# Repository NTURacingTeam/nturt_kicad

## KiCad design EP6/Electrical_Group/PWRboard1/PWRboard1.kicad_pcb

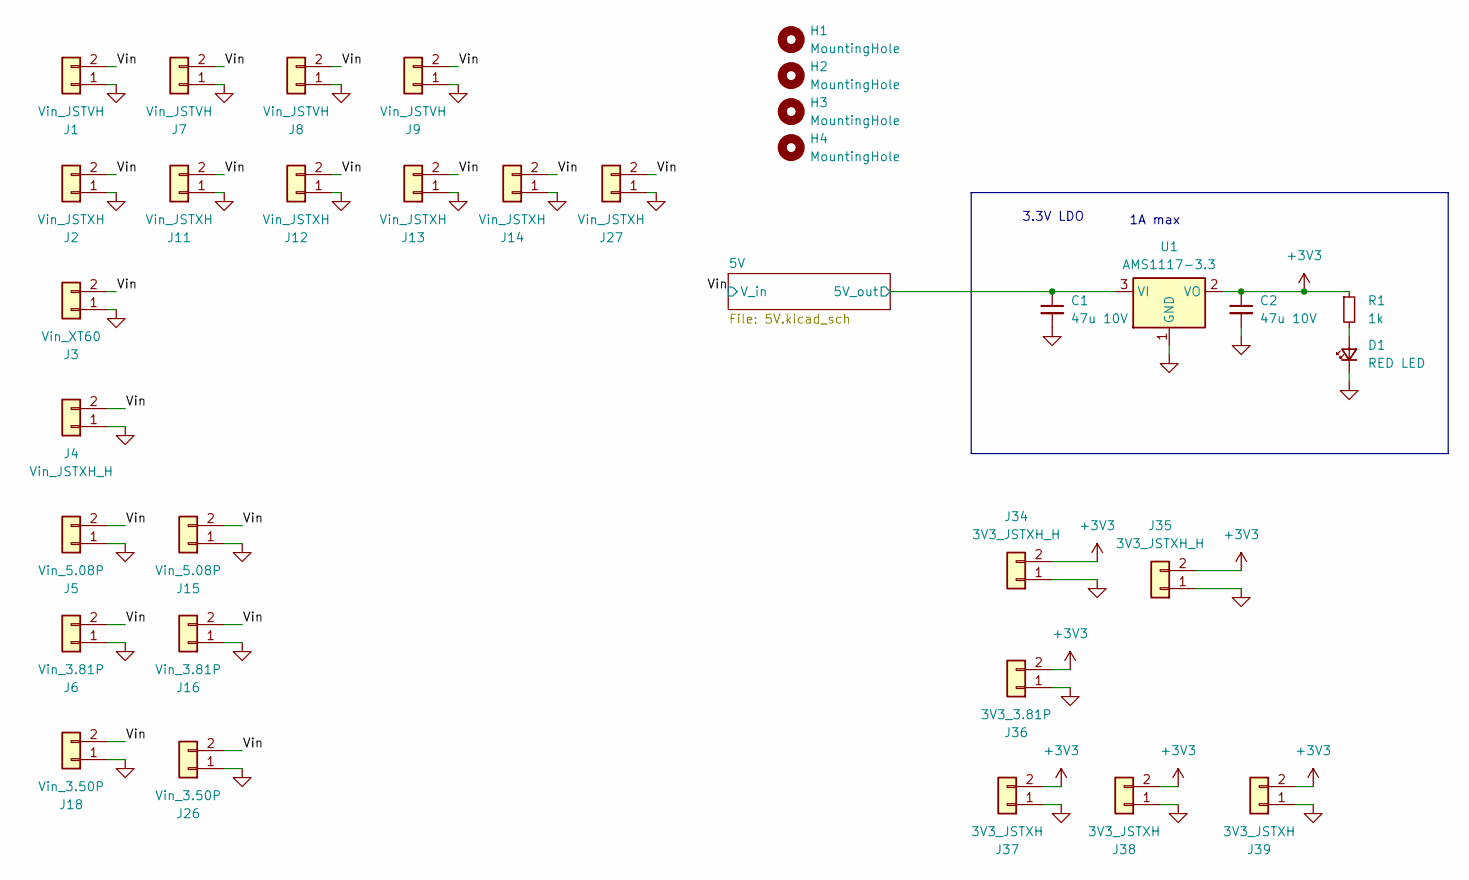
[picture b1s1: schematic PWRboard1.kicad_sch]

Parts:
C1, C2: 47u 10V; C_1206_3216Metric
D1: RED LED; LED_0603_1608Metric
H1, H2, H3, H4: MountingHole; MountingHole_3.2mm_M3
J1, J7, J8, J9: Vin_JSTVH; JST_VH_B2P-VH_1x02_P3.96mm_Vertical
J2, J11, J12, J13, J14, J27: Vin_JSTXH; JST_XH_B2B-XH-A_1x02_P2.50mm_Vertical
J3: Vin_XT60; AMASS_XT60PW-M_1x02_P7.20mm_Horizontal
J4: Vin_JSTXH_H; JST_XH_S2B-XH-A_1x02_P2.50mm_Horizontal
J5, J15: Vin_5.08P; PhoenixContact_MSTBA_2,5_2-G-5,08_1x02_P5.08mm_Horizontal
J6, J16: Vin_3.81P; PhoenixContact_MC_1,5_2-G-3.81_1x02_P3.81mm_Horizontal
J18, J26: Vin_3.50P; PhoenixContact_MC_1,5_2-G-3.5_1x02_P3.50mm_Horizontal
J34, J35: 3V3_JSTXH_H; JST_XH_S2B-XH-A_1x02_P2.50mm_Horizontal
J36: 3V3_3.81P; PhoenixContact_MC_1,5_2-G-3.81_1x02_P3.81mm_Horizontal
J37, J38, J39: 3V3_JSTXH; JST_XH_B2B-XH-A_1x02_P2.50mm_Vertical
R1: 1k; R_0402_1005Metric
U1: AMS1117-3.3; SOT-223-3_TabPin2

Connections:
+3V3: C2.1, J34.2, J35.2, J36.2, J37.2, J38.2, J39.2, R1.1, U1.2 (VO)
/5V/+5V_buck: C1.1, U1.3 (VI); also elsewhere on the board
/Vin: J1.2, J2.2, J3.2, J4.2, J5.2, J6.2, J7.2, J8.2, J9.2, J11.2, J12.2, J13.2, J14.2, J15.2, J16.2, J18.2, J26.2, J27.2; also elsewhere on the board
GND: C1.2, C2.2, D1.1 (K), J1.1, J2.1, J3.1, J4.1, J5.1, J6.1, J7.1, J8.1, J9.1, J11.1, J12.1, J13.1, J14.1, J15.1, J16.1, J18.1, J26.1, J27.1, J34.1, J35.1, J36.1, J37.1, J38.1, J39.1, U1.1 (GND); also elsewhere on the board
unnamed: D1.2 (A), R1.2

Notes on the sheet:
1A max
3.3V LDO

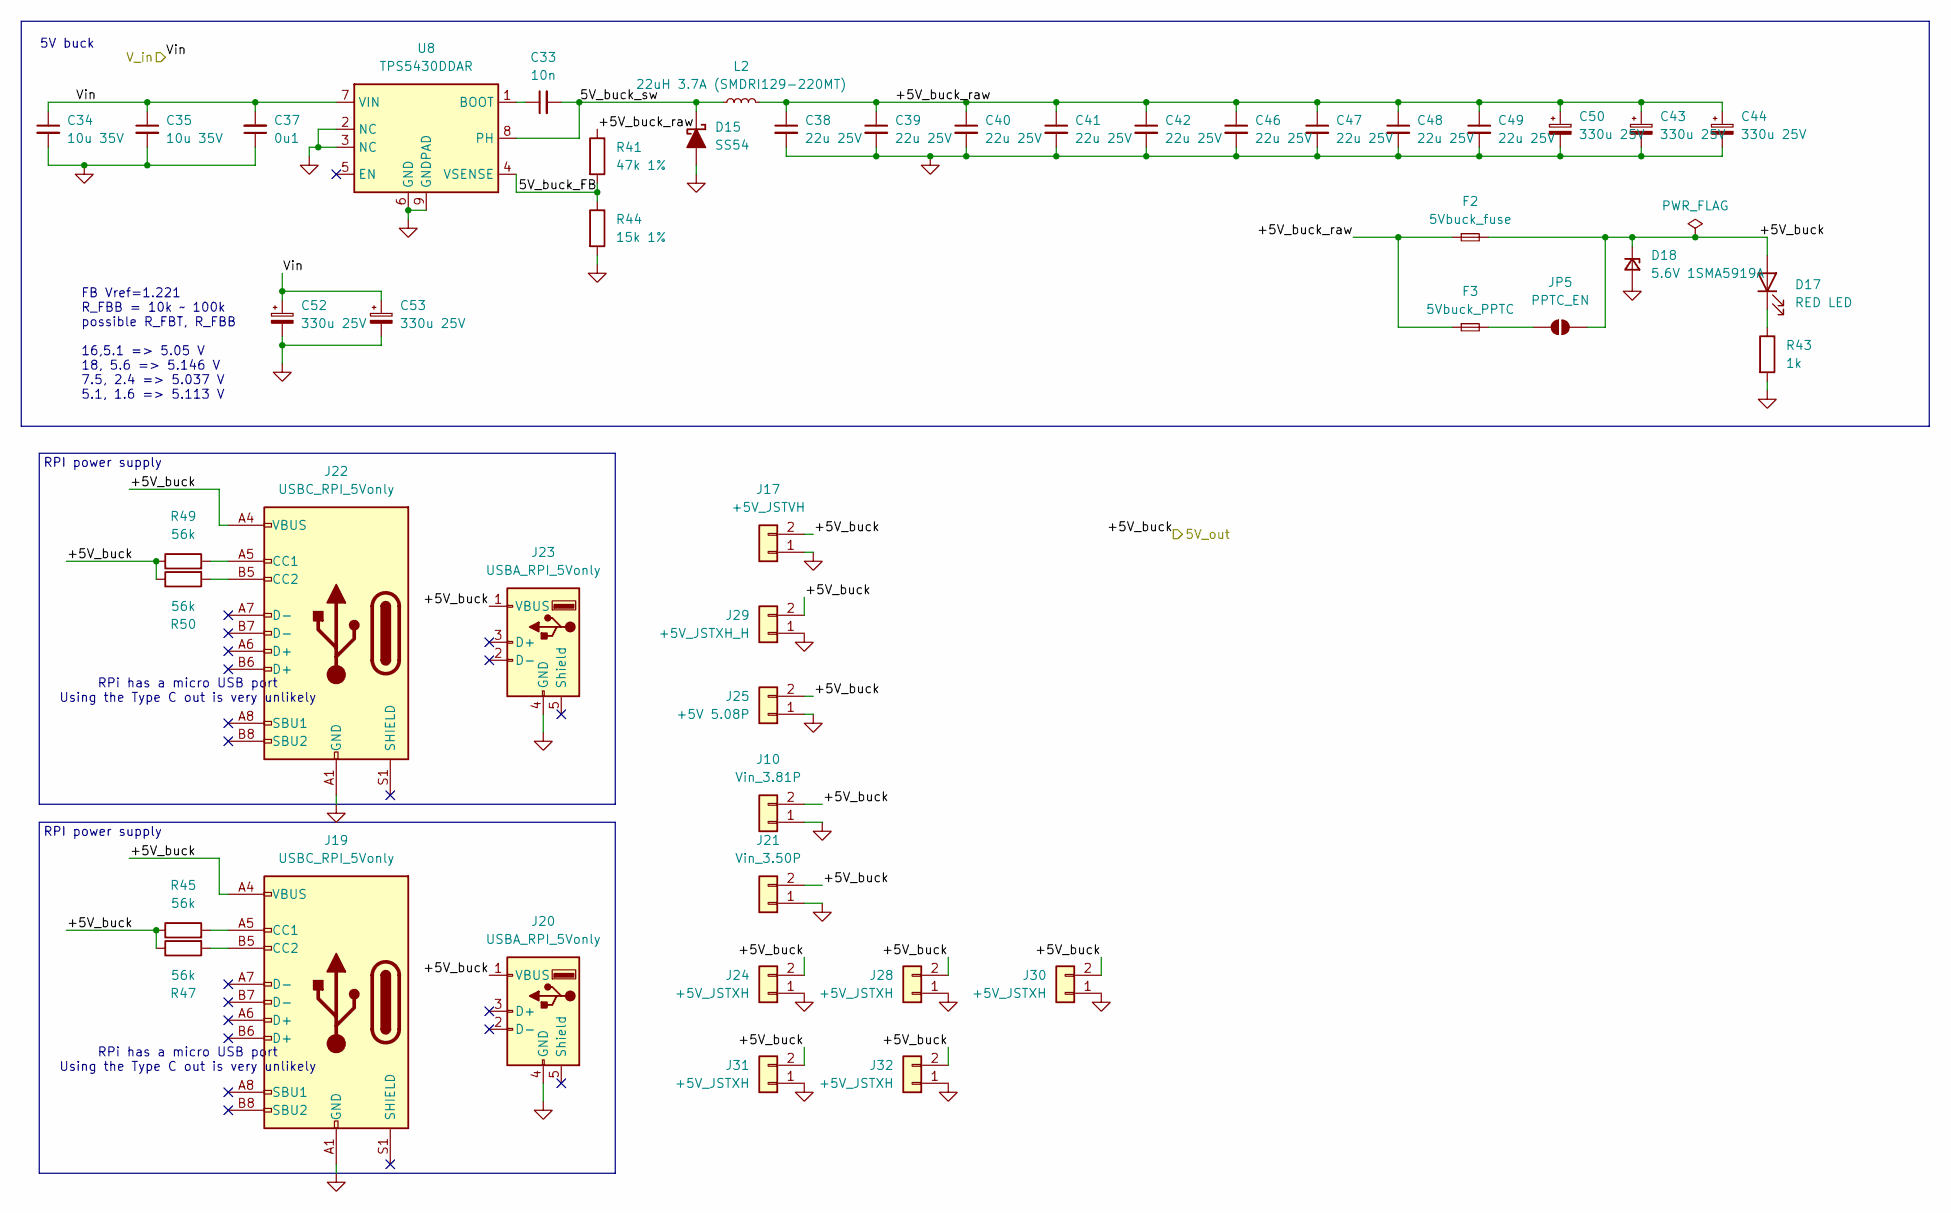
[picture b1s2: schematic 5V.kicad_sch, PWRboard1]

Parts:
C33: 10n; C_0603_1608Metric
C34, C35: 10u 35V; C_1206_3216Metric
C37: 0u1; C_0603_1608Metric
C38, C39, C40, C41, C42, C46, C47, C48, C49: 22u 25V; C_1206_3216Metric
C43, C44, C50, C52, C53: 330u 25V; CP_Radial_D8.0mm_P3.80mm
D15: SS54; D_SMA
D17: RED LED; LED_0603_1608Metric
D18: 5.6V 1SMA5919A; D_SMA
F2: 5Vbuck_fuse; Fuseholder_Cylinder-5x20mm_Stelvio-Kontek_PTF78_Horizontal_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
F3: 5Vbuck_PPTC; Fuse_1206_3216Metric
J10: Vin_3.81P; PhoenixContact_MC_1,5_2-G-3.81_1x02_P3.81mm_Horizontal
J17: +5V_JSTVH; JST_VH_B2P-VH_1x02_P3.96mm_Vertical
J19, J22: USBC_RPI_5Vonly; USB_C_Receptacle_GCT_USB4105-xx-A_16P_TopMnt_Horizontal
J20, J23: USBA_RPI_5Vonly; USB_A_Molex_67643_Horizontal
J21: Vin_3.50P; PhoenixContact_MC_1,5_2-G-3.5_1x02_P3.50mm_Horizontal
J24, J28, J30, J31, J32: +5V_JSTXH; JST_XH_B2B-XH-A_1x02_P2.50mm_Vertical
J25: +5V 5.08P; PhoenixContact_MSTBA_2,5_2-G-5,08_1x02_P5.08mm_Horizontal
J29: +5V_JSTXH_H; JST_XH_S2B-XH-A_1x02_P2.50mm_Horizontal
JP5: PPTC_EN; SolderJumper-2_P1.3mm_Open_RoundedPad1.0x1.5mm
L2: 22uH 3.7A (SMDRI129-220MT); L_Bourns_SRR1260
R41: 47k 1%; R_0603_1608Metric
R43: 1k; R_0402_1005Metric
R44: 15k 1%; R_0603_1608Metric
R45, R47, R49, R50: 56k; R_0402_1005Metric
U8: TPS5430DDAR; TI_SO-PowerPAD-8_ThermalVias

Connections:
/5V/5V_buck_FB: R41.2, R44.1, U8.4 (VSENSE)
/5V/5V_buck_sw: C33.2, D15.1 (K), L2.1, U8.8 (PH)
/5V/+5V_buck: D17.2 (A), D18.1 (K), F2.2, J10.2, J17.2, J19.A4 (VBUS), J19.A9 (VBUS), J19.B4 (VBUS), J19.B9 (VBUS), J20.1 (VBUS), J21.2, J22.A4 (VBUS), J22.A9 (VBUS), J22.B4 (VBUS), J22.B9 (VBUS), J23.1 (VBUS), J24.2, J25.2, J28.2, J29.2, J30.2, J31.2, J32.2, JP5.2 (B), R45.1, R47.1, R49.1, R50.1; also elsewhere on the board
/5V/+5V_buck_raw: C38.1, C39.1, C40.1, C41.1, C42.1, C43.1, C44.1, C46.1, C47.1, C48.1, C49.1, C50.1, F2.1, F3.1, L2.2, R41.1
/Vin: C34.1, C35.1, C37.2, C52.1, C53.1, U8.7 (VIN); also elsewhere on the board
GND: C34.2, C35.2, C37.1, C38.2, C39.2, C40.2, C41.2, C42.2, C43.2, C44.2, C46.2, C47.2, C48.2, C49.2, C50.2, C52.2, C53.2, D15.2 (A), D18.2 (A), J10.1, J17.1, J19.A1 (GND), J19.A12 (GND), J19.B1 (GND), J19.B12 (GND), J20.4 (GND), J21.1, J22.A1 (GND), J22.A12 (GND), J22.B1 (GND), J22.B12 (GND), J23.4 (GND), J24.1, J25.1, J28.1, J29.1, J30.1, J31.1, J32.1, R43.2, R44.2, U8.2 (NC), U8.3 (NC), U8.6 (GND), U8.9 (GNDPAD); also elsewhere on the board
unnamed: D17.1 (K), R43.1
unnamed: J19.A5 (CC1), R45.2
unnamed: J19.B5 (CC2), R47.2
unnamed: J22.A5 (CC1), R49.2
unnamed: J22.B5 (CC2), R50.2
unnamed: F3.2, JP5.1 (A)
unnamed: C33.1, U8.1 (BOOT)

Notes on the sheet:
RPi has a micro USB port Using the Type C out is very unlikely
5V buck
RPI power supply
FB Vref=1.221 R_FBB = 10k ~ 100k possible R_FBT, R_FBB 16,5.1 => 5.05 V 18, 5.6 => 5.146 V 7.5, 2.4 => 5.037 V 5.1, 1.6 => 5.113 V

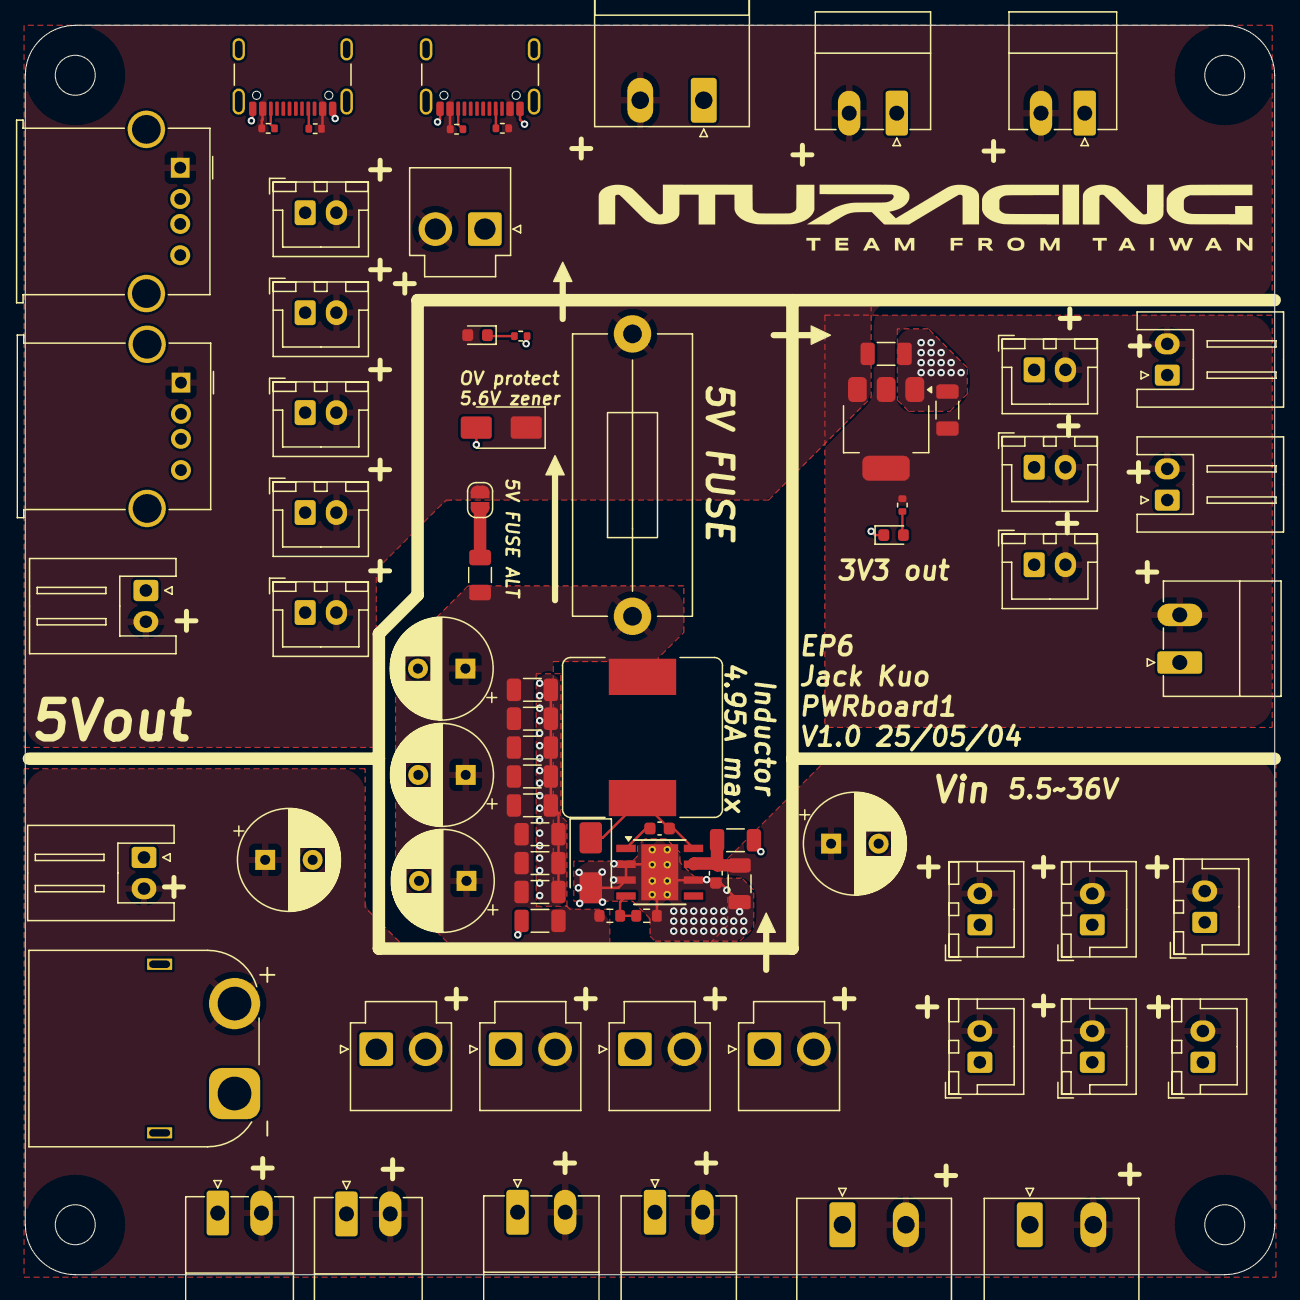
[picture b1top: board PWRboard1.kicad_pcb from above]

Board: 2 copper layers, 100.0 x 100.0 mm, 80 parts (0 on the bottom side), 15 nets.

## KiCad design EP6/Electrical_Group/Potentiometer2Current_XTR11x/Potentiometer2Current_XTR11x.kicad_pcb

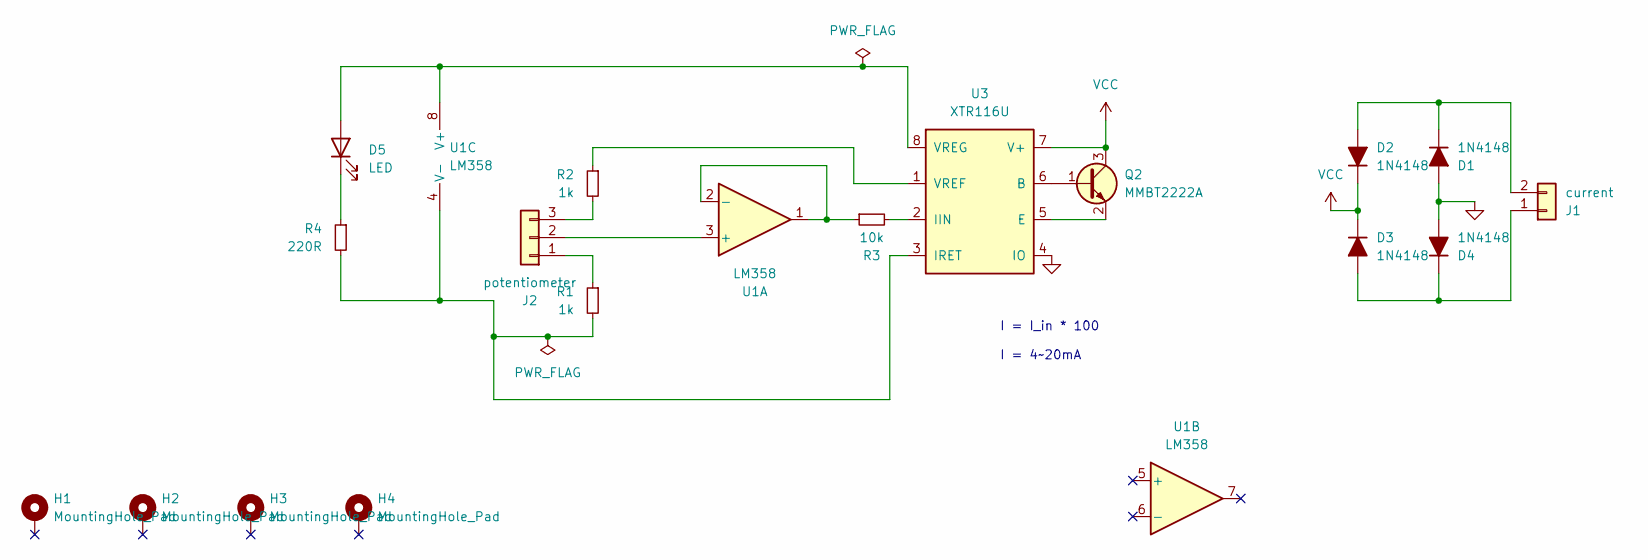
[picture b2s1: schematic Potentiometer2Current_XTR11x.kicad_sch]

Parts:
D1, D2, D3, D4: 1N4148; D_SOD-323
D5: LED; LED_0603_1608Metric
H1, H2, H3, H4: MountingHole_Pad; MountingHole_3.2mm_M3_Pad_TopBottom
J1: current; JST_XH_S2B-XH-A_1x02_P2.50mm_Horizontal; Part Number 1-0201FBV0T
J2: potentiometer; JST_XH_S3B-XH-A_1x03_P2.50mm_Horizontal
Q2: MMBT2222A; SOT-23
R1, R2: 1k; R_0402_1005Metric
R3: 10k; R_0402_1005Metric
R4: 220R; R_0402_1005Metric
U1: LM358; SOIC-8_3.9x4.9mm_P1.27mm
U3: XTR116U; SOIC-8_3.9x4.9mm_P1.27mm

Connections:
GND: D1.2 (A), D4.2 (A), U3.4 (IO)
unnamed: D1.1 (K), D2.2 (A), J1.2
unnamed: D3.2 (A), D4.1 (K), J1.1
unnamed: D5.2 (A), U1.8 (V+), U3.8 (VREG)
unnamed: D5.1 (K), R4.1
unnamed: J2.1, R1.1
unnamed: J2.2, U1.3 (+)
unnamed: J2.3, R2.2
unnamed: Q2.1 (B), U3.6 (B)
unnamed: Q2.2 (E), U3.5 (E)
unnamed: R3.1, U1.1, U1.2 (-)
unnamed: R1.2, R4.2, U1.4 (V-), U3.3 (IRET)
unnamed: R3.2, U3.2 (IIN)
unnamed: R2.1, U3.1 (VREF)
VCC: D2.1 (K), D3.1 (K), Q2.3 (C), U3.7 (V+)

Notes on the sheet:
I = I_in * 100 I = 4~20mA

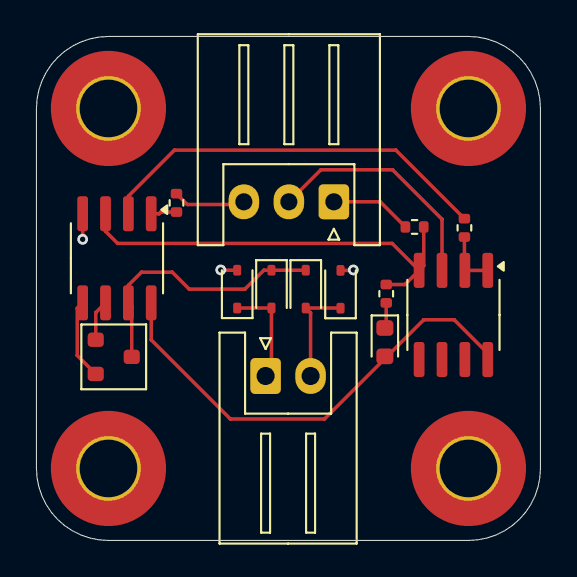
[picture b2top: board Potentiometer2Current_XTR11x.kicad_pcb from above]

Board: 2 copper layers, 28.0 x 28.0 mm, 18 parts (0 on the bottom side), 15 nets.

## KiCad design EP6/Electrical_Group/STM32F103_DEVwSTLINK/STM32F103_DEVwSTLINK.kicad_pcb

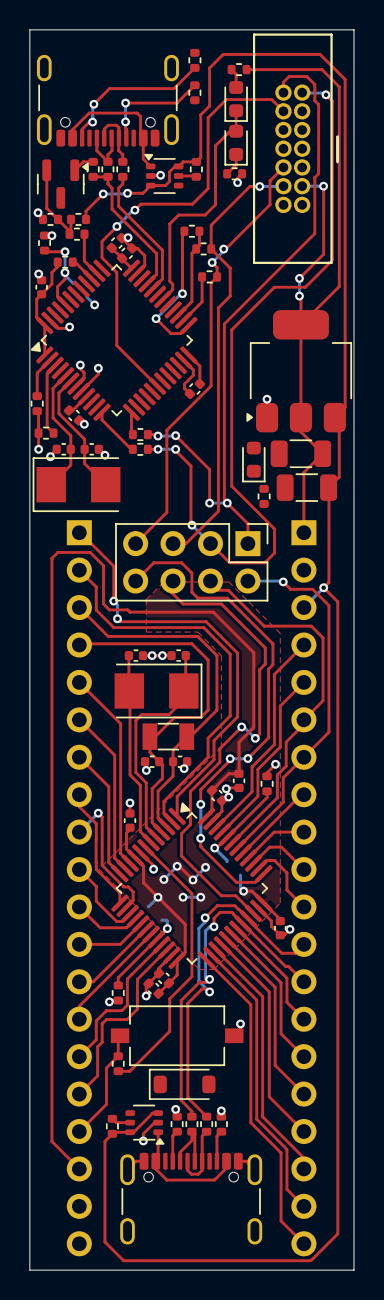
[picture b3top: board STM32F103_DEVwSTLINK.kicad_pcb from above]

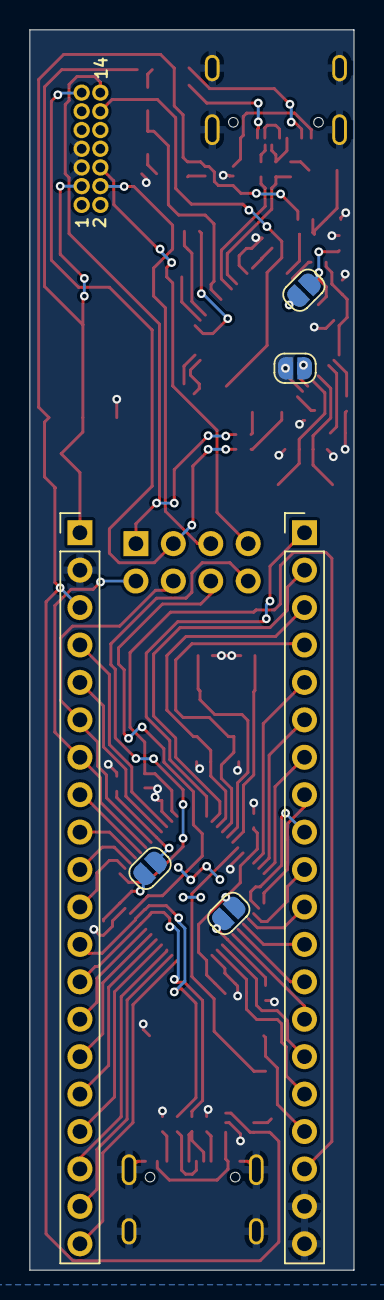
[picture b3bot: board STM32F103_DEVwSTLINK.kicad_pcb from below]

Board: 2 copper layers, 22.0 x 84.2 mm, 72 parts (6 on the bottom side), 82 nets.

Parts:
C1, C2, C3: 10u 6V; C_0402_1005Metric
C5, C6, C7, C8, C15, C16, C17, C18: 0u1; C_0402_1005Metric
C9, C10: 33p; C_0402_1005Metric
C11, C12: 15p; C_0402_1005Metric
C19, C20: 30p; C_0402_1005Metric
C21, C22: 47u 10V; C_1206_3216Metric
D1: EMERALD led; LED_0603_1608Metric
D2: 3.3V 123 (BZT52B3V3); D_SOD-123
D3: RED 3V3; LED_0603_1608Metric
D4: RED led; LED_0603_1608Metric
J1, J4: USB_C_stm32; USB_C_Receptacle_GCT_USB4105-xx-A_16P_TopMnt_Horizontal
J2, J3: Conn_01x20; PinHeader_1x20_P2.54mm_Vertical
J5: STDC14; box_header_14P_pitch127
J6: DEBUG; PinHeader_2x04_P2.54mm_Vertical
JP1, JP3: BOOT0; SolderJumper-2_P1.3mm_Open_RoundedPad1.0x1.5mm
JP2: BOOT1; SolderJumper-2_P1.3mm_Open_RoundedPad1.0x1.5mm
JP4: RESET; SolderJumper-2_P1.3mm_Open_RoundedPad1.0x1.5mm
Q1: SS9013; SOT-23
R1, R4, R7, R8: 22R; R_0402_1005Metric
R2, R5, R10: 100k; R_0402_1005Metric
R3, R11, R13, R18, R20, R26: 10k; R_0402_1005Metric
R9, R15: 220R; R_0402_1005Metric
R12, R14, R27, R28: 10R; R_0402_1005Metric
R16, R17, R23, R24: 5k1; R_0402_1005Metric
R19, R21: 100R; R_0402_1005Metric
R22: 39k; R_0402_1005Metric
R25: 1k5; R_0402_1005Metric
R29: 4k7; R_0402_1005Metric
R31: 1k; R_0402_1005Metric
SW1: RESET; SW_Tactile_SPST_NO_Straight_CK_PTS636Sx25SMTRLFS
U1: STM32F103CBTx; LQFP-48_7x7mm_P0.5mm
U2: STM32F103CBT6; LQFP-48_7x7mm_P0.5mm
U3, U5: LM66100DCK; SOT-363_SC-70-6
U4: AMS1117-3.3; SOT-223-3_TabPin2
Y1, Y3: 8MHz X50328MSB2GI; Crystal_SMD_5032-2Pin_5.0x3.2mm
Y2: 32.768kHz Q13FC13500004; Crystal_SMD_3215-2Pin_3.2x1.5mm

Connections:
+3V3: C1.1, C2.1, C3.1, C5.1, C6.1, C7.1, C8.1, C15.1, C16.1, C17.1, C18.1, C22.1, D2.1 (K), D3.2 (A), J2.18, J3.1, J5.3, JP1.2 (B), JP2.2 (B), JP3.2 (B), Q1.3 (C), R9.1, R29.1, U1.9 (VDDA), U1.24 (VDD), U1.36 (VDD), U1.48 (VDD), U2.1 (VBAT), U2.9 (VDDA), U2.24 (VDD), U2.36 (VDD), U2.48 (VDD), U4.2 (VO)
+5V: C21.1, J3.3, R18.1, R20.1, R26.1, U3.3 (~CE), U3.6 (VOUT), U4.3 (VI), U5.3 (~CE), U5.6 (VOUT)
/MCU/3VB: J2.1, U1.1 (VBAT)
/MCU/BOOT0: JP1.1 (A), R5.1, U1.44 (BOOT0)
/MCU/BOOT1: JP2.1 (A), R2.1, U1.20 (PB2)
/MCU/NRST: R3.2, U1.7 (NRST)
/MCU/OSC32_IN: C11.1, J2.3, U1.3 (PC14), Y2.1
/MCU/OSC32_OUT: C12.1, J2.4, U1.4 (PC15), Y2.2
/MCU/OSC_IN: C9.1, U1.5 (PD0), Y1.1
/MCU/OSC_OUT: C10.1, U1.6 (PD1), Y1.2
/MCU/PA0: J2.5, U1.10 (PA0)
/MCU/PA1: J2.6, U1.11 (PA1)
/MCU/PA2: J2.7, U1.12 (PA2)
/MCU/PA3: J2.8, U1.13 (PA3)
/MCU/PA4: J2.9, U1.14 (PA4)
/MCU/PA5: J2.10, U1.15 (PA5)
/MCU/PA6: J2.11, U1.16 (PA6)
/MCU/PA7: J2.12, U1.17 (PA7)
/MCU/PA8: J3.16, U1.29 (PA8)
/MCU/PA9: J3.15, U1.30 (PA9)
/MCU/PA10: J3.14, U1.31 (PA10)
/MCU/PA13: J6.6, U1.34 (PA13)
/MCU/PA14: J6.8, U1.37 (PA14)
/MCU/PA15: J3.11, U1.38 (PA15)
/MCU/PB0: J2.13, U1.18 (PB0)
/MCU/PB1: J2.14, U1.19 (PB1)
/MCU/PB3: J3.10, U1.39 (PB3)
/MCU/PB4: J3.9, U1.40 (PB4)
/MCU/PB5: J3.8, U1.41 (PB5)
/MCU/PB6: J3.7, J6.2, U1.42 (PB6)
/MCU/PB7: J3.6, J6.4, U1.43 (PB7)
/MCU/PB8: J3.5, U1.45 (PB8)
/MCU/PB9: J3.4, U1.46 (PB9)
/MCU/PB10: J2.15, U1.21 (PB10)
/MCU/PB11: J2.16, U1.22 (PB11)
/MCU/PB12: J3.20, U1.25 (PB12)
/MCU/PB13: J3.19, U1.26 (PB13)
/MCU/PB14: J3.18, U1.27 (PB14)
/MCU/PB15: J3.17, U1.28 (PB15)
/MCU/PC13: J2.2, U1.2 (PC13)
/MCU/RESET: J2.17, R3.1, SW1.1
/MCU/USB_D+: J1.A6 (D+), J1.B6 (D+), R14.2
/MCU/USB_D-: J1.A7 (D-), J1.B7 (D-), R12.2
/MCU/USB_DN: J3.13, R12.1, U1.32 (PA11)
/MCU/USB_DP: J3.12, R14.1, U1.33 (PA12)
/MCU/VBUS: J1.A4 (VBUS), J1.A9 (VBUS), J1.B4 (VBUS), J1.B9 (VBUS), U5.1 (VIN)
/STlink/BOOT0: JP3.1 (A), R10.1, U2.44 (BOOT0)
/STlink/LED_STLINK: D1.1 (K), D4.2 (A), U2.30 (PA9)
/STlink/NRST: JP4.1 (A), U2.7 (NRST)
/STlink/OSC_IN: C19.1, U2.5 (PD0), Y3.1
/STlink/OSC_OUT: C20.1, U2.6 (PD1), Y3.2
/STlink/USART2_RX: R4.1, U2.13 (PA3)
/STlink/USART2_TX: R1.1, U2.12 (PA2)
/STlink/USB_D+: J4.A6 (D+), J4.B6 (D+), R28.2
/STlink/USB_D-: J4.A7 (D-), J4.B7 (D-), R27.2
/STlink/USB_DN: R27.1, U2.32 (PA11)
/STlink/USB_DP: R25.2, R28.1, U2.33 (PA12)
/STlink/USB_nRENUM: R21.1, U2.38 (PA15)
/STlink/VBUS: J4.A4 (VBUS), J4.A9 (VBUS), J4.B4 (VBUS), J4.B9 (VBUS), U3.1 (VIN)
/STlink/t_CLK: R7.1, U2.26 (PB13)
/STlink/t_DIO: R8.1, R19.1, U2.27 (PB14)
/STlink/t_DIO_IN: R19.2, U2.25 (PB12)
/T_NRST: J5.12, U2.18 (PB0)
/T_SWCLK: J5.6, J6.7, R7.2
/T_SWDIO: J5.4, J6.5, R8.2
/T_VCP_RX: J5.13, J6.3, R1.2
/T_VCP_TX: J5.14, J6.1, R4.2
GND: C1.2, C2.2, C3.2, C5.2, C6.2, C7.2, C8.2, C9.2, C10.2, C11.2, C12.2, C15.2, C16.2, C17.2, C18.2, C19.2, C20.2, C21.2, C22.2, D2.2 (A), J1.A1 (GND), J1.A12 (GND), J1.B1 (GND), J1.B12 (GND), J1.S1 (SHIELD), J2.19, J2.20, J3.2, J4.A1 (GND), J4.A12 (GND), J4.B1 (GND), J4.B12 (GND), J4.S1 (SHIELD), J5.5, J5.7, JP4.2 (B), R2.2, R5.2, R10.2, R11.2, R13.2, R15.2, R16.1, R17.1, R22.2, R23.1, R24.1, R31.2, SW1.2, U1.8 (VSSA), U1.23 (VSS), U1.35 (VSS), U1.47 (VSS), U2.8 (VSSA), U2.20 (PB2), U2.23 (VSS), U2.35 (VSS), U2.47 (VSS), U3.2 (GND), U4.1 (GND), U5.2 (GND)
unnamed: D1.2 (A), R9.2
unnamed: D3.1 (K), R31.1
unnamed: D4.1 (K), R15.1
unnamed: J1.A5 (CC1), R16.2
unnamed: J1.B5 (CC2), R17.2
unnamed: J4.A5 (CC1), R23.2
unnamed: J4.B5 (CC2), R24.2
unnamed: Q1.2 (B), R20.2, R21.2, R22.1
unnamed: Q1.1 (E), R25.1
unnamed: R29.2, U2.39 (PB3)
unnamed: R11.1, U2.2 (PC13)
unnamed: R13.1, U2.3 (PC14)
unnamed: R18.2, U3.5 (ST)
unnamed: R26.2, U5.5 (ST)

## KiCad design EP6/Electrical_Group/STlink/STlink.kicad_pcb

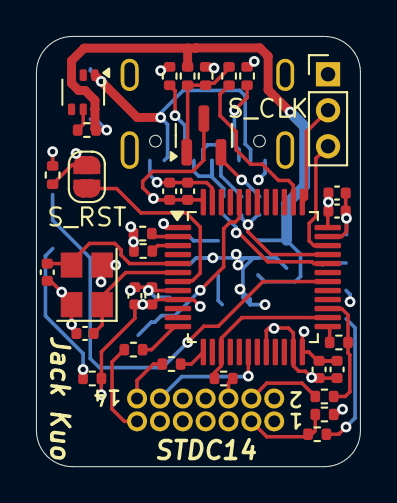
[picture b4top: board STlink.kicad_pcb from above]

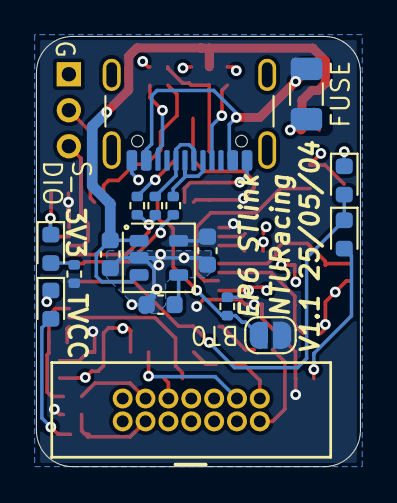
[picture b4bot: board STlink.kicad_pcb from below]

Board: 4 copper layers, 18.0 x 23.9 mm, 50 parts (17 on the bottom side), 39 nets.

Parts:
C1, C2: 1u; C_0603_1608Metric
C3: 22n; C_0603_1608Metric
C4, C5, C6, C7: 10u 6V; C_0402_1005Metric
C8, C9, C10, C11: 0u1; C_0402_1005Metric
C12, C13: 30p; C_0402_1005Metric
D1: BLUE LED; LED_0603_1608Metric
D2: RED LED; LED_0603_1608Metric
D3: GREEN led; LED_0603_1608Metric
D4: RED led; LED_0603_1608Metric
F1: 0.5A; Fuse_1206_3216Metric
J1: STDC14; box_header_14P_pitch127
J2: S_SWD; PinHeader_1x03_P2.00mm_Vertical
J3: USB_C_stm32; USB_C_Receptacle_GCT_USB4105-xx-A_16P_TopMnt_Horizontal
JP1: S_RESET; SolderJumper-2_P1.3mm_Open_RoundedPad1.0x1.5mm
JP2: BOOT0; SolderJumper-2_P1.3mm_Open_RoundedPad1.0x1.5mm
Q1: MMBT3904; SOT-23
R1: 0R; R_0402_1005Metric
R2, R3: 1k; R_0402_1005Metric
R5, R6, R8, R9, R23, R24: 20R; R_0402_1005Metric
R10, R14: 220R; R_0402_1005Metric
R11: 100k; R_0402_1005Metric
R12, R13, R15, R17: 10k; R_0402_1005Metric
R16, R18: 100R; R_0402_1005Metric
R19: 33k; R_0402_1005Metric
R20, R21: 5k1; R_0402_1005Metric
R22: 1k5; R_0402_1005Metric
U1: RT9193; SOT-23-5
U2: STM32F103CBT6; LQFP-48_7x7mm_P0.5mm
U3: LM66100DCK; SOT-363_SC-70-6
Y2: 8MHz; Crystal_SMD_3225-4Pin_3.2x2.5mm

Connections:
+3V3: C2.1, C4.1, C5.1, C6.1, C7.1, C8.1, C9.1, C10.1, C11.1, JP2.2 (B), Q1.3 (C), R1.1, R3.1, R10.1, U1.5 (OUT), U2.1 (VBAT), U2.9 (VDDA), U2.24 (VDD), U2.36 (VDD), U2.48 (VDD)
+5V: C1.1, F1.2, R15.1, R17.1, U1.1 (IN), U1.3 (EN), U3.3 (~CE), U3.6 (VOUT)
/STlink/BOOT0: JP2.1 (A), R11.1, U2.44 (BOOT0)
/STlink/LED_STLINK: D3.1 (K), D4.2 (A), U2.30 (PA9)
/STlink/OSC_IN: C12.1, U2.5 (PD0), Y2.3
/STlink/OSC_OUT: C13.1, U2.6 (PD1), Y2.1
/STlink/RENUM: R18.1, U2.38 (PA15)
/STlink/S_CLK: J2.2, U2.37 (PA14)
/STlink/S_DIO: J2.3, U2.34 (PA13)
/STlink/S_NRST: JP1.2 (B), U2.7 (NRST)
/STlink/USART2_RX: R6.1, U2.13 (PA3)
/STlink/USART2_TX: R5.1, U2.12 (PA2)
/STlink/USB_D+: J3.A6 (D+), J3.B6 (D+), R24.1
/STlink/USB_D-: J3.A7 (D-), J3.B7 (D-), R23.1
/STlink/USB_DN: R23.2, U2.32 (PA11)
/STlink/USB_DP: R22.2, R24.2, U2.33 (PA12)
/STlink/VBUS: F1.1, J3.A4 (VBUS), J3.A9 (VBUS), J3.B4 (VBUS), J3.B9 (VBUS), U3.1 (VIN)
/STlink/t_CLK: R8.1, U2.15 (PA5), U2.26 (PB13)
/STlink/t_DIO: R9.1, R16.1, U2.27 (PB14)
/T_3V3: J1.3, R1.2, R2.1
/T_NRST: J1.12, U2.18 (PB0)
/T_SWCLK: J1.6, R8.2
/T_SWDIO: J1.4, R9.2
/T_VCP_RX: J1.13, R5.2
/T_VCP_TX: J1.14, R6.2
GND: C1.2, C2.2, C3.2, C4.2, C5.2, C6.2, C7.2, C8.2, C9.2, C10.2, C11.2, C12.2, C13.2, D1.1 (K), D2.1 (K), J1.5, J1.7, J2.1, J3.A1 (GND), J3.A12 (GND), J3.B1 (GND), J3.B12 (GND), JP1.1 (A), R11.2, R12.2, R13.2, R14.2, R19.2, R20.1, R21.1, U1.2, U2.8 (VSSA), U2.20 (PB2), U2.23 (VSS), U2.35 (VSS), U2.47 (VSS), U3.2 (GND), Y2.2, Y2.4
unnamed: D1.2 (A), R2.2
unnamed: D2.2 (A), R3.2
unnamed: D3.2 (A), R10.2
unnamed: D4.1 (K), R14.1
unnamed: J3.A5 (CC1), R20.2
unnamed: J3.B5 (CC2), R21.2
unnamed: Q1.1 (B), R17.2, R18.2, R19.1
unnamed: Q1.2 (E), R22.1
unnamed: C3.1, U1.4 (BYP)
unnamed: R16.2, U2.25 (PB12)
unnamed: R12.1, U2.2 (PC13)
unnamed: R13.1, U2.3 (PC14)
unnamed: R15.2, U3.5 (ST)

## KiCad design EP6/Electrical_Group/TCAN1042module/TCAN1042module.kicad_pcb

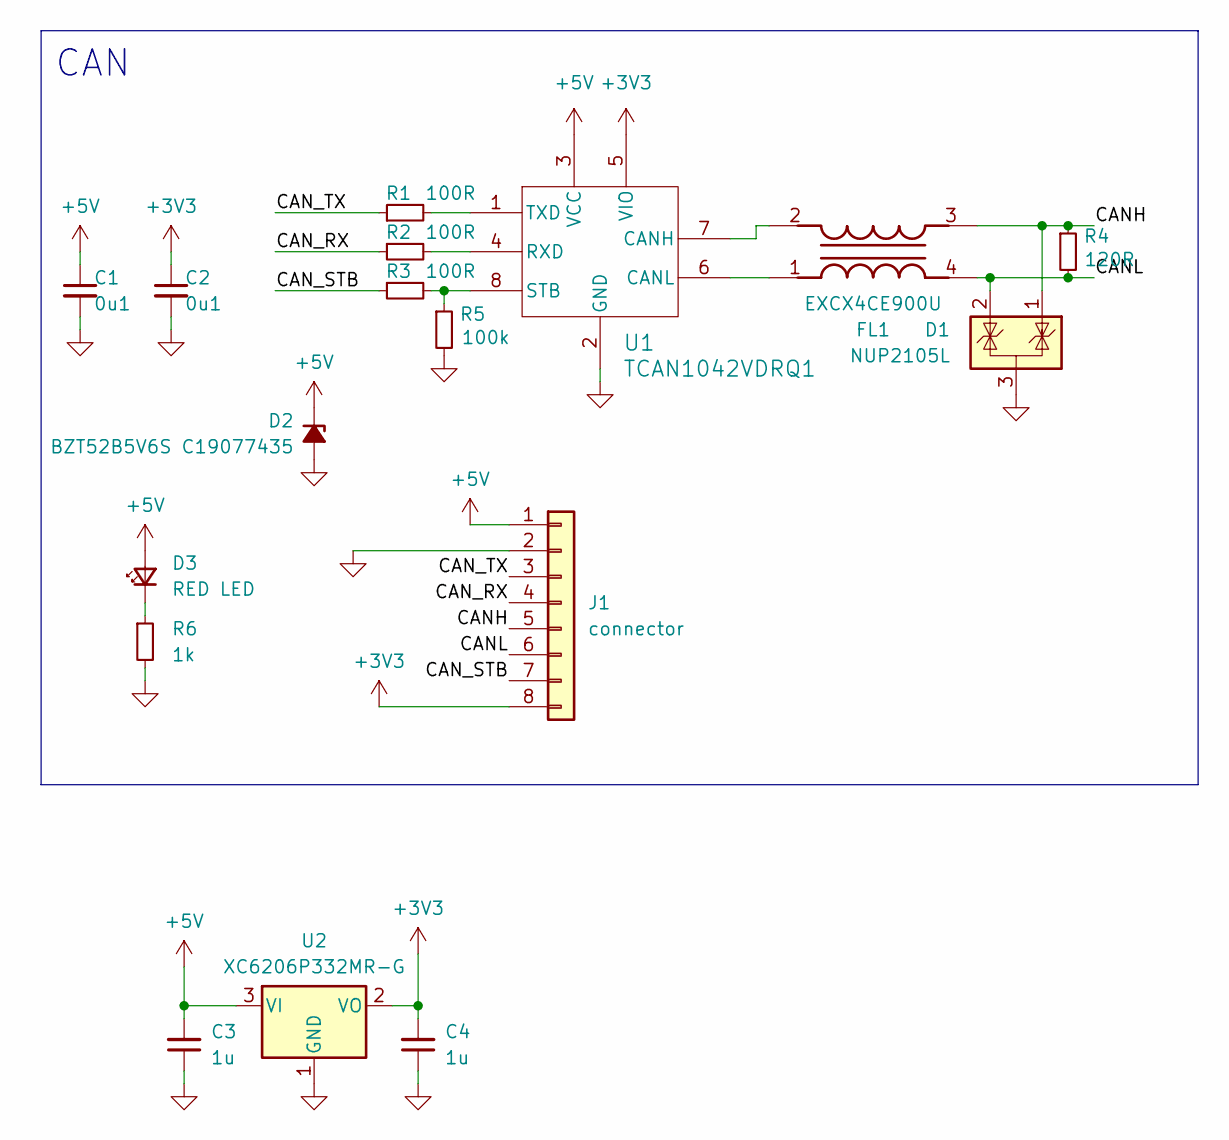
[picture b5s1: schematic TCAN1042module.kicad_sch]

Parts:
C1, C2: 0u1; C_0402_1005Metric
C3, C4: 1u; C_0402_1005Metric
D1: NUP2105L; SOT-23
D2: BZT52B5V6S C19077435; D_SOD-323
D3: RED LED; LED_0603_1608Metric
FL1: EXCX4CE900U; Mouser Part Number 667-EXC-X4CE900U
J1: connector; PinHeader_1x08_P2.54mm_Vertical
R1, R2, R3: 100R; R_0402_1005Metric
R4: 120R; R_0402_1005Metric
R5: 100k; R_0402_1005Metric
R6: 1k; R_0402_1005Metric
U1: TCAN1042VDRQ1; SOIC-8_3.9x4.9mm_P1.27mm
U2: XC6206P332MR-G; SOT-23-3

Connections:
+3V3: C2.1, C4.2, J1.8, U1.5 (VIO), U2.2 (VO)
+5V: C1.1, C3.2, D2.1 (K), D3.2 (A), J1.1, U1.3 (VCC), U2.3 (VI)
/CANH: D1.1 (K), FL1.3, J1.5, R4.1
/CANL: D1.2 (K), FL1.4, J1.6, R4.2
/CAN_RX: J1.4, R2.1
/CAN_STB: J1.7, R3.1
/CAN_TX: J1.3, R1.1
GND: C1.2, C2.2, C3.1, C4.1, D1.3 (A), D2.2 (A), J1.2, R5.2, R6.2, U1.2 (GND), U2.1 (GND)
unnamed: D3.1 (K), R6.1
unnamed: FL1.2, U1.7 (CANH)
unnamed: FL1.1, U1.6 (CANL)
unnamed: R2.2, U1.4 (RXD)
unnamed: R3.2, R5.1, U1.8 (STB)
unnamed: R1.2, U1.1 (TXD)

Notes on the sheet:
CAN

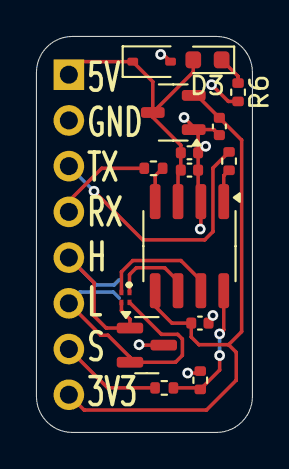
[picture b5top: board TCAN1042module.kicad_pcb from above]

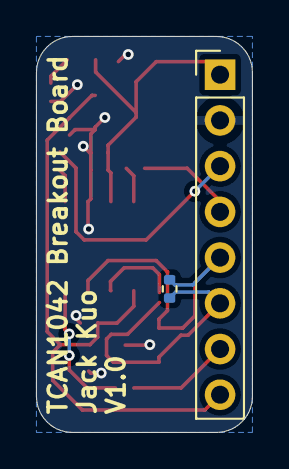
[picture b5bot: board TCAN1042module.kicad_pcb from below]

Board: 2 copper layers, 12.0 x 22.0 mm, 17 parts (2 on the bottom side), 14 nets.
